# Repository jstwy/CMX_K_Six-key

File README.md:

# CMX K Six-key
**Repository Organization**  
[`CMX_K_Six-Key.PCBDesignFiles`](https://github.com/jstwy/CMX_K_Six-key/tree/master/CMX_K_Six-Key.PCBDesignFiles) contains KiCAD files (schematic, PCB, and Gerber files)  
[`CMX_K_Six-Key.Firmware`](https://github.com/jstwy/CMX_K_Six-key/tree/master/CMX_K_Six-key.Firmware) contains firmware files (tmk_core submodule, configuration files, and compiled hex file)  
`CMX_K_Six-Key.Enclosure` contains enclosure design files (to be created...)

## PCB  
The design was done using KiCAD, following [ruiqimao's Keyboard PCB Guide](https://github.com/ruiqimao/keyboard-pcb-guide). The PCB was manufactured by [Oshpark](https://oshpark.com/) and hand-populated with components purchased from [Digi-Key Electronics](https://www.digikey.ca/), as listed in the [BOM](../master/CMX_K_Six-Key.BOM.csv).

## Firmware  
The keypad firmware was built using [tmk's TMK Keyboard Firmware Core Library](https://github.com/tmk/tmk_core), following [matt3o's keyboard firmware guide](https://deskthority.net/viewtopic.php?f=7&t=7177&start=). A virtual Linux Ubuntu machine was used to compile and flash the code.

Although the datasheet for the microcontroller indicates that the part used in this project, the ATMEGA32U4RC-AU, comes with a USB bootloader pre-programmed (see page 422 of the [datasheet](http://ww1.microchip.com/downloads/en/DeviceDoc/Atmel-7766-8-bit-AVR-ATmega16U4-32U4_Datasheet.pdf)), my microcontroller did not come with one. For that reason, I had to solder wires onto the SPI signal pins and the reset pin in order to program the microcontroller with an Arduino UNO [set up as an in-system programmer](https://www.arduino.cc/en/tutorial/arduinoISP).

The AVRDUDE command to program the fuses is:  
`avrdude -p m32u4 -P COM8 -c avrisp -b 19200 -U lfuse:w:0xff:m -U hfuse:w:0x98:m -U efuse:w:0xf7:m`  
where `COM8` is the COM port that my Arduino UNO was connected to.

The AVRDUDE command to flash the firmware is:  
`avrdude -p m32u4 -P COM8 -c avrisp -b 19200 -U flash:w:ATMega32U4-usbdevice_dfu-1_0_0.hex`  
where `ATMega32U4-usbdevice_dfu-1_0_0.hex` is the name of my hex file.

## Enclosure  
This part of the project has not been completed yet.

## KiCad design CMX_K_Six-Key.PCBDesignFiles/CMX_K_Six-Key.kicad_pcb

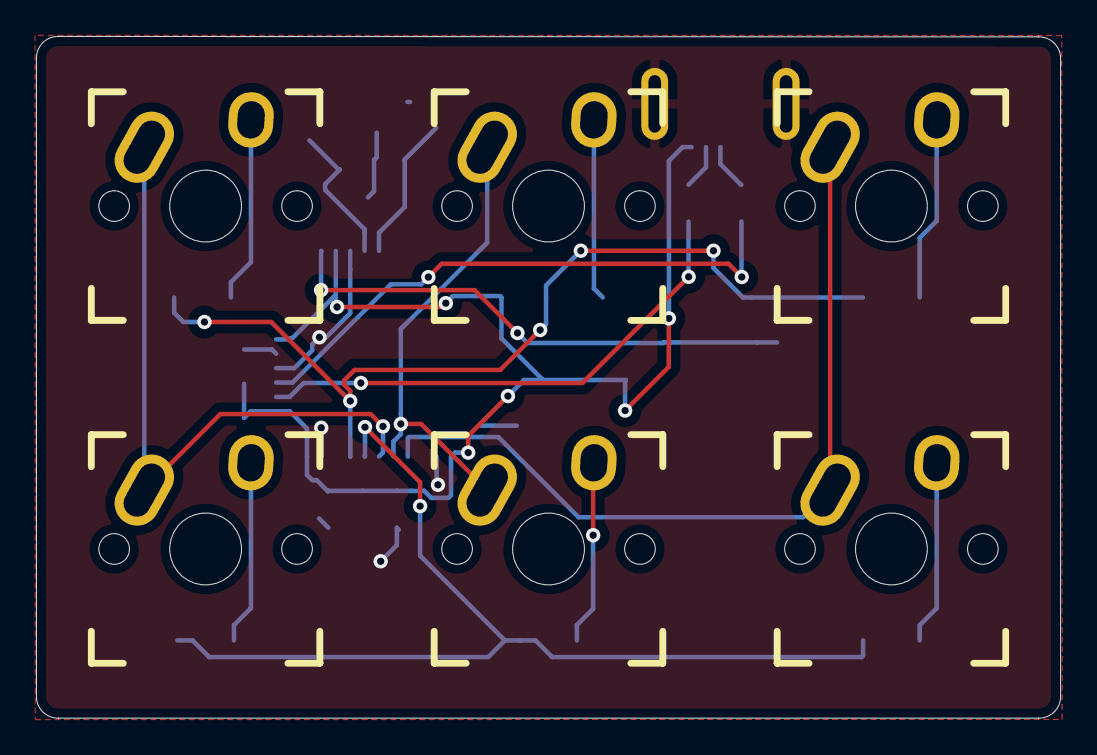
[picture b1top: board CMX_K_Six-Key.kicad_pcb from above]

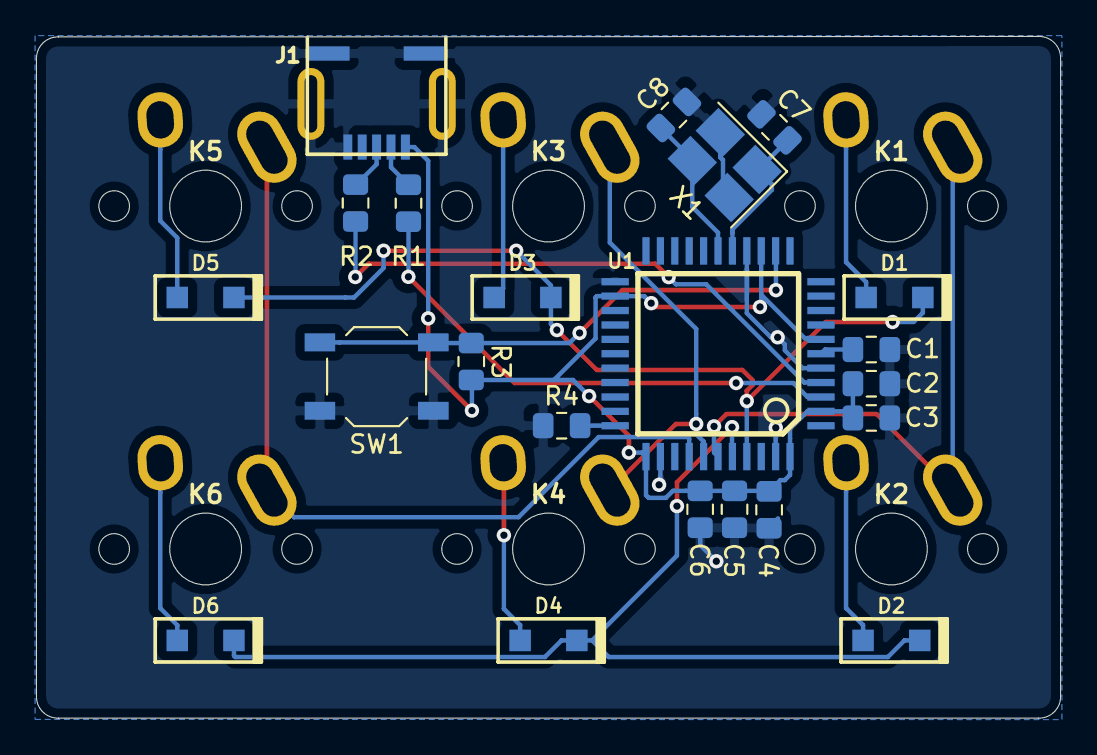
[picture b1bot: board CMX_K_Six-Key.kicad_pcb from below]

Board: 2 copper layers, 56.9 x 37.9 mm, 28 parts (22 on the bottom side), 22 nets.

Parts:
C1: 1u; C_0805_2012Metric_Pad1.15x1.40mm_HandSolder
C2, C3, C4, C5: 0.1u; C_0805_2012Metric_Pad1.15x1.40mm_HandSolder
C6: 4.7u; C_0805_2012Metric_Pad1.15x1.40mm_HandSolder
C7, C8: 22p; C_0805_2012Metric_Pad1.15x1.40mm_HandSolder
D1, D2, D3, D4, D5, D6: D; D_SOD123_hand
J1: USB_mini_micro_B; USB_miniB_hirose_5S8
K1, K2, K3, K4, K5, K6: KEYSW; Mx_Alps_100
R1, R2: 22; R_0805_2012Metric_Pad1.15x1.40mm_HandSolder
R3, R4: 10k; R_0805_2012Metric_Pad1.15x1.40mm_HandSolder
SW1: SW_PUSH; SW_SPST_TL3342
U1: ATMEGA32U4; QFP44
X1: XTAL_GND; Crystal_SMD_SeikoEpson_FA238-4Pin_3.2x2.5mm_HandSoldering

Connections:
/COL0: K1.1, K2.1, U1.39
/COL1: K3.1, K4.1, U1.38
/COL2: K5.1, K6.1, U1.37
/D+: R2.1, U1.4
/D-: R1.1, U1.3
/ROW0: D1.1, D3.1, D5.1, U1.41
/ROW1: D2.1, D4.1, D6.1, U1.40
/UCAP: C1.2, U1.6
/VUSB: C2.1, C3.1, C4.1, C5.1, C6.1, J1.1, R3.2, U1.2, U1.7, U1.14, U1.24, U1.34, U1.44
/XTAL1: C7.1, U1.16, X1.1
/XTAL2: C8.1, U1.17, X1.3
/~HWB~: R4.2, U1.33
/~RESET~: R3.1, SW1.2, U1.13
GND: C1.1, C2.2, C3.2, C4.2, C5.2, C6.2, C7.2, C8.2, J1.5, J1.6, R4.1, SW1.1, U1.5, U1.15, U1.23, U1.35, U1.43, X1.2, X1.4
unnamed: D1.2, K1.2
unnamed: D2.2, K2.2
unnamed: D3.2, K3.2
unnamed: D4.2, K4.2
unnamed: D5.2, K5.2
unnamed: D6.2, K6.2
unnamed: J1.2, R1.2
unnamed: J1.3, R2.2

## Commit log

2019-09-01 Upload directory - PCB design files
2019-09-02 Upload file - PDF of schematic
2019-09-03 Upload - firmware files w/o tmk_core
2019-09-17 Upload new hex, config.h, keymap.c, and Makefile
2019-09-17 Add submodule tmk_core
2019-09-20 Update README with FW building guide
2019-09-20 Update README formatting
2019-09-20 Updated README formatting
2019-09-20 Updated README with more info
2019-09-20 Updated README with better formatting
2019-09-20 removed line from README
2019-09-20 changed README "tmk" to "t.m.k."
2019-12-08 uploaded BOM
2019-12-08 updated readme with more documentation
